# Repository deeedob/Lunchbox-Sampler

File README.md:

# Lunchbox Sampler

## Prerequisites

- [platformio](https://platformio.org/)
    - Teensyduino >= 1.58
    - gcc-arm-none-eabi >= 11.3.1

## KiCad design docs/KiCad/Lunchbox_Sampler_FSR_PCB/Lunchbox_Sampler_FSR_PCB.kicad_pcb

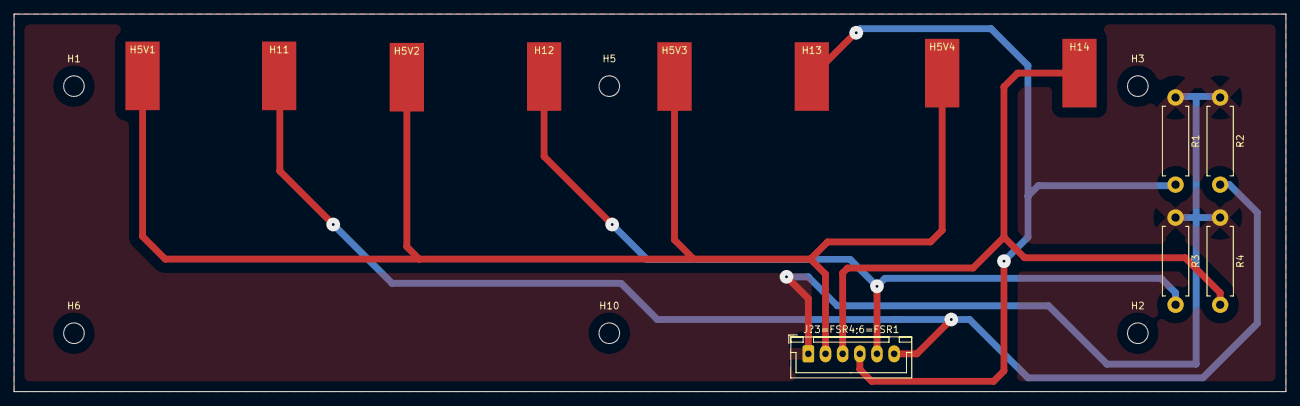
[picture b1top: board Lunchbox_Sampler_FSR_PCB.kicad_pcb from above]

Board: 2 copper layers, 185.3 x 55.0 mm, 19 parts (0 on the bottom side), 6 nets.

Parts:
H1, H2, H3, H5, H6, H10: MountingHole; MountingHole_3mm
H5V1, H5V2, H5V3, H5V4, H11, H12, H13, H14: MountingHole_Pad; SolderWirePad_1x01_SMD_5x10mm
J?3=FSR4;6=FSR1: 06JQ-BT; JST_XH_B6B-XH-A_1x06_P2.50mm_Vertical
R1, R2, R3, R4: R_Variable; R_Axial_DIN0411_L9.9mm_D3.6mm_P12.70mm_Horizontal

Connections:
GND: J?3=FSR4;6=FSR1.1, R1.1, R2.1, R3.1, R4.1
unnamed: H5V1.1, H5V2.1, H5V3.1, H5V4.1, J?3=FSR4;6=FSR1.2
unnamed: H11.1, J?3=FSR4;6=FSR1.6, R2.2
unnamed: H12.1, J?3=FSR4;6=FSR1.5, R3.2
unnamed: H13.1, J?3=FSR4;6=FSR1.4, R1.2
unnamed: H14.1, J?3=FSR4;6=FSR1.3, R4.2

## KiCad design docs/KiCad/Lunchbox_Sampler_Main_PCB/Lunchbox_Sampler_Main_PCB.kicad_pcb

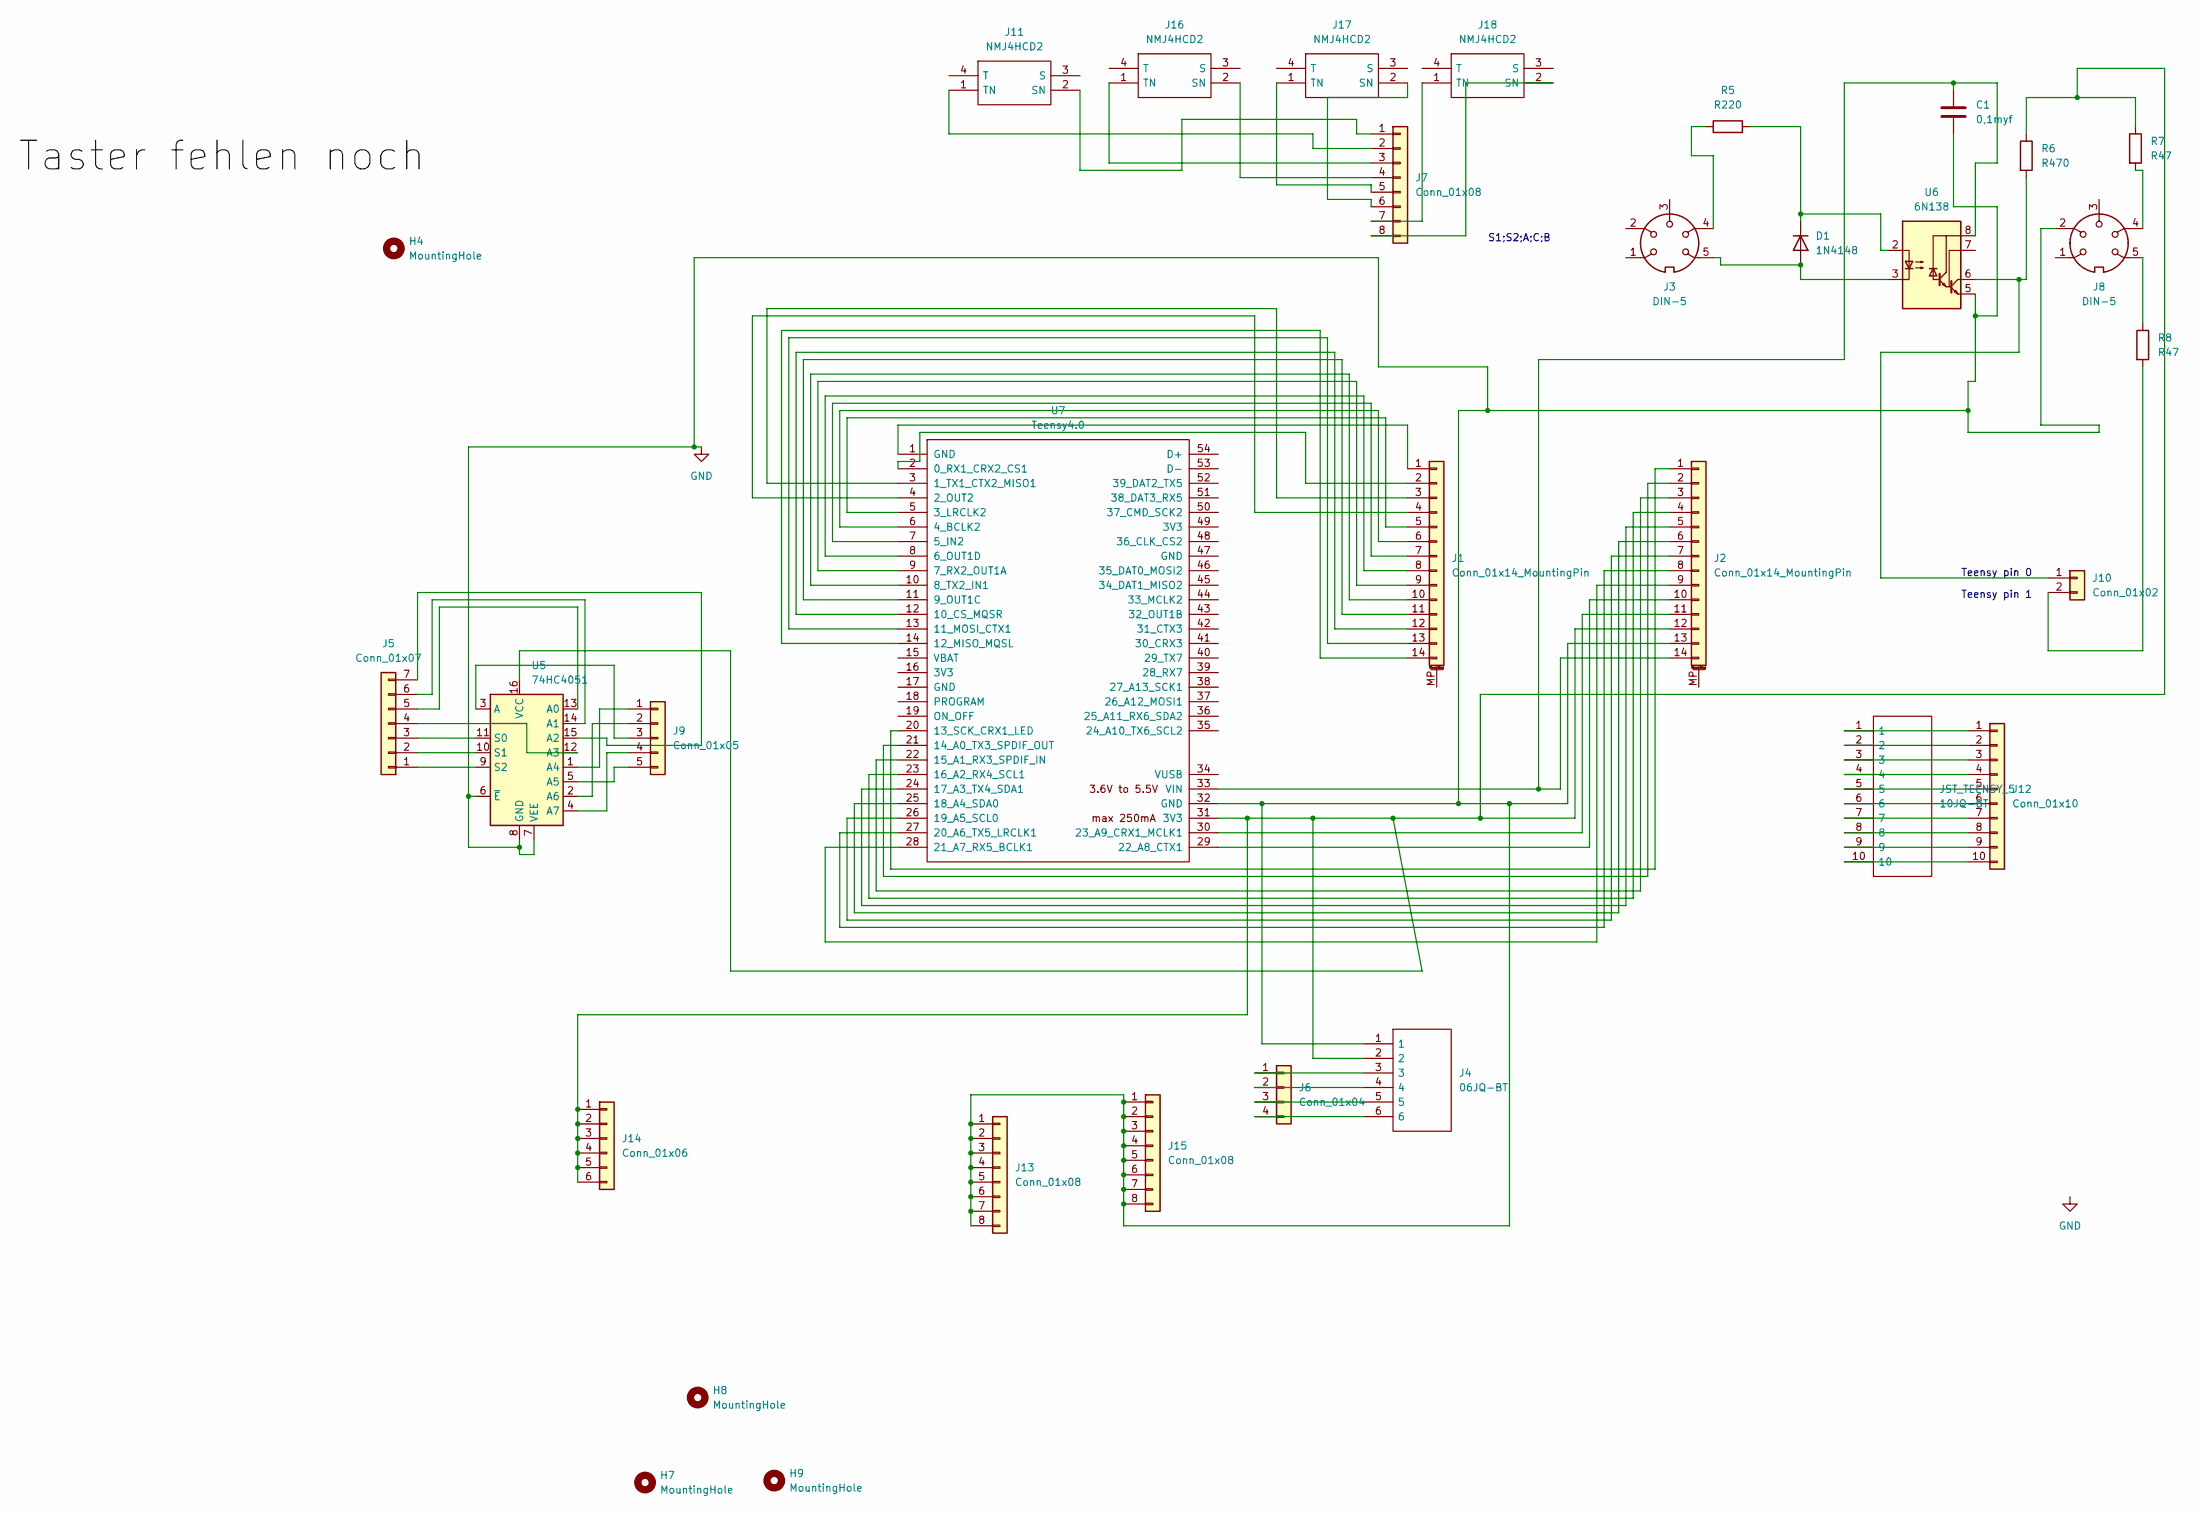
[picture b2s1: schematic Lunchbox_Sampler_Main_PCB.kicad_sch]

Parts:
C1: 0,1myf; CP_Radial_D8.0mm_P5.00mm
D1: 1N4148; D_DO-35_SOD27_P7.62mm_Horizontal
H4, H7, H8, H9: MountingHole; MountingHole_3mm
J1, J2: Conn_01x14_MountingPin; PinHeader_1x14_P2.54mm_Vertical
J3, J8: DIN-5; SDS-50J_MIDI_JACK
J4: 06JQ-BT; JST_XH_B6B-XH-A_1x06_P2.50mm_Vertical; Manufacturer_Part_Number 06JQ-BT
J5: Conn_01x07; PinHeader_1x07_P2.54mm_Vertical
J6: Conn_01x04; PinHeader_1x04_P2.54mm_Vertical
J7, J13, J15: Conn_01x08; PinHeader_1x08_P2.54mm_Vertical
J9: Conn_01x05; PinHeader_1x05_P2.54mm_Vertical
J10: Conn_01x02; PinHeader_1x02_P2.54mm_Vertical
J11, J16, J17, J18: NMJ4HCD2; Mouser Part Number 550-12202
J12: Conn_01x10; PinHeader_1x10_P2.54mm_Vertical
J14: Conn_01x06; PinHeader_1x06_P2.54mm_Vertical
JST_TEENSY_5: 10JQ-BT; JST_SH_SM10B-SRSS-TB_1x10-1MP_P1.00mm_Horizontal; Manufacturer_Part_Number 10JQ-BT; Mouser Part Number N/A
R5: R220; R_Axial_DIN0411_L9.9mm_D3.6mm_P12.70mm_Horizontal
R6: R470; R_Axial_DIN0411_L9.9mm_D3.6mm_P12.70mm_Horizontal
R7, R8: R47; R_Axial_DIN0411_L9.9mm_D3.6mm_P12.70mm_Horizontal
U5: 74HC4051; DIP794W53P254L1930H508Q16N
U6: 6N138; DIP762W56P254L966H508Q8N
U7: Teensy4.0; Teensy40

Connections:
GND: C1.2, J2.13, J4.1, J8.2, J13.1, J13.2, J13.3, J13.4, J13.5, J13.6, J13.7, J13.8, J15.1, J15.2, J15.3, J15.4, J15.5, J15.6, J15.7, J15.8, U5.6 (~E), U5.7 (VEE), U5.8 (GND), U6.5 (GND), U7.32 (GND)
unnamed: C1.1, J2.14, U6.8 (VCC), U7.33 (VIN)
unnamed: D1.1 (K), R5.2, U6.2 (C1)
unnamed: D1.2 (A), J3.5, U6.3 (C2)
unnamed: J1.1, U7.1 (GND)
unnamed: J1.2, U7.2 (0_RX1_CRX2_CS1)
unnamed: J1.3, U7.3 (1_TX1_CTX2_MISO1)
unnamed: J1.4, U7.4 (2_OUT2)
unnamed: J1.5, U7.5 (3_LRCLK2)
unnamed: J1.6, U7.6 (4_BCLK2)
unnamed: J1.7, U7.7 (5_IN2)
unnamed: J1.8, U7.8 (6_OUT1D)
unnamed: J1.9, U7.9 (7_RX2_OUT1A)
unnamed: J1.10, U7.10 (8_TX2_IN1)
unnamed: J1.11, U7.11 (9_OUT1C)
unnamed: J1.12, U7.12 (10_CS_MQSR)
unnamed: J1.13, U7.13 (11_MOSI_CTX1)
unnamed: J1.14, U7.14 (12_MISO_MQSL)
unnamed: J2.1, U7.20 (13_SCK_CRX1_LED)
unnamed: J2.2, U7.21 (14_A0_TX3_SPDIF_OUT)
unnamed: J2.3, U7.22 (15_A1_RX3_SPDIF_IN)
unnamed: J2.4, U7.23 (16_A2_RX4_SCL1)
unnamed: J2.5, U7.24 (17_A3_TX4_SDA1)
unnamed: J2.6, U7.25 (18_A4_SDA0)
unnamed: J2.7, U7.26 (19_A5_SCL0)
unnamed: J2.8, U7.27 (20_A6_TX5_LRCLK1)
unnamed: J2.9, U7.28 (21_A7_RX5_BCLK1)
unnamed: J2.10, U7.29 (22_A8_CTX1)
unnamed: J2.11, U7.30 (23_A9_CRX1_MCLK1)
unnamed: J3.4, R5.1
unnamed: J4.3, J6.1
unnamed: J4.4, J6.2
unnamed: J4.5, J6.3
unnamed: J4.6, J6.4
unnamed: J5.1, U5.9 (S2)
unnamed: J5.2, U5.10 (S1)
unnamed: J5.3, U5.11 (S0)
unnamed: J5.4, U5.12 (A3)
unnamed: J5.5, U5.13 (A0)
unnamed: J5.6, U5.14 (A1)
unnamed: J5.7, U5.15 (A2)
unnamed: J8.4, R7.2
unnamed: J8.5, R8.1
unnamed: J9.1, U5.1 (A4)
unnamed: J9.2, U5.2 (A6)
unnamed: J9.3, U5.3 (A)
unnamed: J9.4, U5.4 (A7)
unnamed: J9.5, U5.5 (A5)
unnamed: J10.1, R6.2, U6.6 (VO2)
unnamed: J10.2, R8.2
unnamed: J7.2, J11.1 (TN)
unnamed: J7.1, J11.2 (SN)
unnamed: J12.1, JST_TEENSY_5.1
unnamed: J12.2, JST_TEENSY_5.2
unnamed: J12.3, JST_TEENSY_5.3
unnamed: J12.4, JST_TEENSY_5.4
unnamed: J12.5, JST_TEENSY_5.5
unnamed: J12.6, JST_TEENSY_5.6
unnamed: J12.7, JST_TEENSY_5.7
unnamed: J12.8, JST_TEENSY_5.8
unnamed: J12.9, JST_TEENSY_5.9
unnamed: J12.10, JST_TEENSY_5.10
unnamed: J2.12, J4.2, J14.1, J14.2, J14.3, J14.4, J14.5, J14.6, R6.1, R7.1, U5.16 (VCC), U7.31 (3V3)
unnamed: J7.3, J16.1 (TN)
unnamed: J7.4, J16.2 (SN)
unnamed: J7.5, J17.1 (TN)
unnamed: J7.6, J17.2 (SN)
unnamed: J7.7, J18.1 (TN)
unnamed: J7.8, J18.2 (SN)

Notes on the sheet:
Teensy pin 1
Teensy pin 0
S1;S2;A;C;B

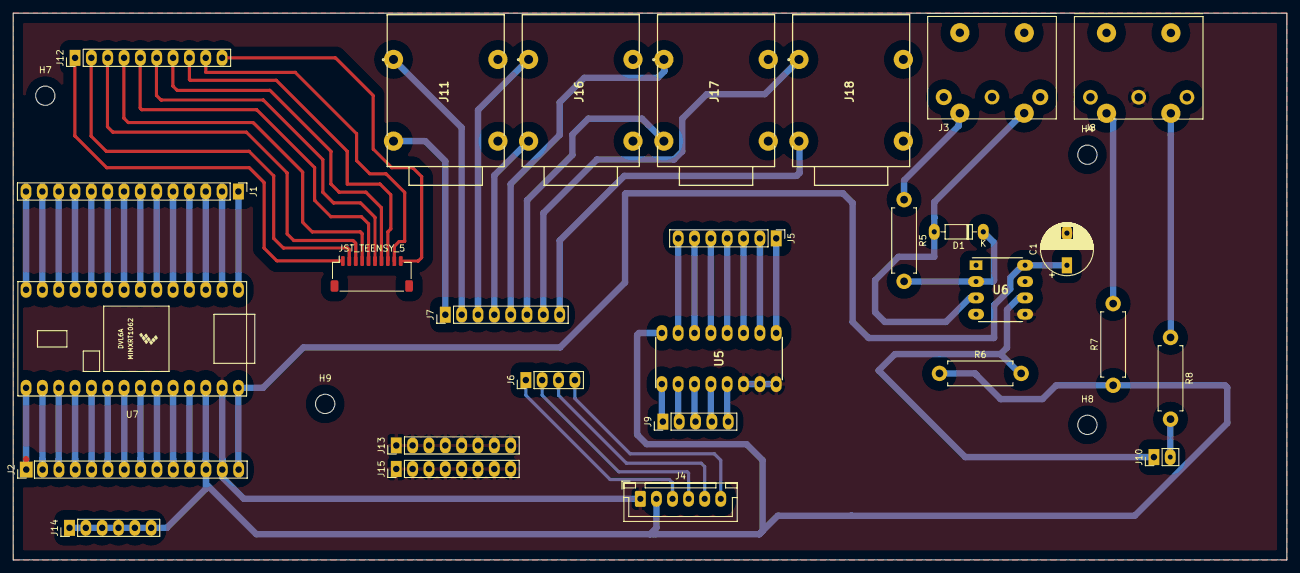
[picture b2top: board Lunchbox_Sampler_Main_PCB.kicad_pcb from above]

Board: 2 copper layers, 198.0 x 85.0 mm, 32 parts (0 on the bottom side), 68 nets.

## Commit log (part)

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2022-05-16 all test outcommented, execpt for loop
2022-05-16 wait until All Files are deleted
2022-05-17 minorChangesMemory
2022-05-20 Search Free Midi with Array, Print in .txt
2022-05-20 Update Settings as Array, Write in settings.txt;
2022-05-21 getSettings
2022-05-21 load settings update
2022-05-21 interrupt handler
2022-05-22 Comment and update Settings.txt when File is deleted
2022-06-09 Installing missing libraries and cleaning up headers
2022-06-09 Ignore CMakeLists.txt
2022-06-09 Revert platformio dependencies: Something is not quite right
2022-06-09 Move memory functions to own class
2022-06-12 defines
2022-06-12 Adjusting platformio.ini to needs (dependencies)
2022-06-12 Rewriting test.cpp to fit with newly created memory classes
2022-06-12 rtos
2022-06-12 Outsource of memory functions to own class (code still to be refactored)
2022-06-14 event-system structure
2022-06-14 interrupt handler impl
2022-06-15 started analog interrupts
2022-06-16 temporary commit outsourced Midi Class
2022-06-16 MemGeneric improve Singleton
2022-06-16 MemGeneric improve Singleton Part 2 (hpp)
2022-06-17 resolved circ dependencies -> dependency_graph.py!
2022-06-27 cleanup
2022-06-27 resources for testing
2022-06-27 Instruction for building the test
2022-06-27 fixed display bug
2022-06-27 print
2022-06-27 Update Hardware Test, test Flash
2022-06-27 multiplexer test
2022-06-28 Working stage: Memory Class (chaotic)
2022-06-28 docs
2022-06-28 remove latex docs
2022-06-28 pcb_case informations
2022-06-28 testing pins
2022-06-29 MemoryClass still chaotic no 2
2022-06-29 code review
2022-06-29 multiplexer working
2022-06-30 testing host midi
2022-06-30 pcb & case layout optimization
2022-06-30 started midi host testing
2022-06-30 todo - print and midi together
2022-07-02 fsr :: pin layout :: event rework
2022-07-02 fdps
2022-07-02 fsr and pots in seperate classes
2022-07-03 Interrupt System finished :: testing
2022-07-03 digital interrupt and audio working, no audio glitches!!
2022-07-04 using glue routines *_*, analog almost working
2022-07-05 Changing Singleton classes from pointer to reference
2022-07-05 analog and digital interrupts working
2022-07-05 fsr, pots, digital everything is working!! WTF
2022-07-07 pdfs
2022-07-21 event system almost completed
2022-07-22 preparing for big merge
2022-07-22 merged interrupts into main
2022-07-22 RecordMidi test
2022-07-22 prepareing for unidocs merge
2022-07-22 Huge chaos, much changes also in software design... status: testing of csv parsing done and working stable
2022-07-22 Refactoring of software design: introducing new classes MemSample unifying MemFlash and MemSD class (higher level abstraction class)
2022-07-22 preparing for main merge
2022-07-22 merged MIDI branch into main
2022-07-22 merged MemoryClass into main
2022-07-22 merged hw-test into main
2022-07-22 merged midi-host into main
2022-07-22 big changes :: refactores the whole repo structure :: please consult the README
2022-07-22 cleanup :: added clang-format :: LICENSE
2022-07-22 added main Application
2022-07-22 readme
2022-07-22 restored midi branch
2022-07-22 main dev branch
2022-07-23 added .idea for clion files
2022-07-23 readme, clion setup guide
2022-07-23 added srcFilter
2022-07-24 License : GPLv3 :: moved Doxyfile to docs :: rm .idea
2022-07-24 removed clang-format for now :: added clang-tidy
2022-07-24 clang-tidy
2022-07-24 Added Kicad Project
2022-07-24 added Kicad Files
2022-07-24 .gitignore
2022-07-24 KiCad Cleanup
2022-07-24 src_filter :: tidy -> fn now camelCase
2022-07-24 clang format and internal naming conventions in project setting
2022-07-24 Updated Kicad Project
2022-07-25 event system 99% finished
2022-07-25 hotfix
2022-07-25 restored memory branch
2022-07-25 structured and added interactive tests
2022-07-25 structured and added interactive tests, updated KiCad files
2022-07-26 event system now working with lbs singleton instance!
2022-07-26 Midi record update
2022-07-26 midi update
2022-07-26 created simple notes class
2022-07-26 fixed bug in pots
2022-07-26 update testing record Overdub
2022-07-26 Event System 100% working 100% integrated!
2022-08-03 multiple changes for Memory Class, forgotten to do subsequent commits
2022-08-08 update Notes Overdub
2022-08-08 Add library to play sound from Flash
2022-08-08 Add File interface for writing to MemFlash
2022-08-08 Add interface for reading File from SD to MemSD
2022-08-08 Finish loadSamplePack function and first drafts for playback
2022-08-08 Untrack original memory class files
2022-08-08 Removed SoundZ (does not compile) and friend function for playback added
2022-08-11 recordmidiinternnogrid
2022-08-12 changed code style :: pots now take const * const pointer
2022-08-12 rewrite of graphics system
2022-08-12 remove inner classes to write and read files, restructure with friend functions
2022-08-12 boolean --> bool
2022-08-12 started midi lib
2022-08-13 custom fonts :: graphics lib improvement
2022-08-13 window system impl
2022-08-14 rewrote graphics system :: added basic modules
2022-08-15 working on modules
2022-08-15 latest Kicad Project files
2022-08-16 update playSample (moved to MemFlash) and fix different problems in function declarations (some classes did not associate function with their implementation)
2022-08-16 load SamplePack01 for testing
2022-08-16 restructured modules
2022-08-16 improved PCB for soldering parts
2022-08-17 modules working almost 100%
2022-08-17 removed old lbs-ui
2022-08-17 modules need implementation
2022-08-17 updated fontconverter
2022-08-17 updated from dev
2022-08-17 added samplepack
2022-08-18 initialized new module
2022-08-18 structured memory module
2022-08-18 New Memory classes under lbs-memory, big restructure
2022-08-18 remove unused code
2022-08-18 remove Singleton
2022-08-18 line break
2022-08-18 Switch to new memory class
2022-08-18 test load File to flash and getFileList
2022-08-18 started audio impl
2022-08-18 Flash Pin and FlashSize, Settings file and Samplepack dir define constants in define_t40.hpp
2022-08-18 Copy constructor fix in Window class (Adafruit bug on lucas' machine)
2022-08-18 Basename function to mem_flash
2022-08-19 fixed weird Adafruit GFX bug
2022-08-19 Midi Visualisation static
2022-08-19 Midi Visualisation still static,but display of send in note
2022-08-20 add eraseFlash function
2022-08-20 fix Window bug in Copy Constructor: adjust prototype in class definition (remove width and height from copy constructor prototype)
2022-08-20 2ns try, error on merging from origin/memorymain: fix Window bug in Copy Constructor: adjust prototype in class definition (remove width and height from copy constructor prototype)
2022-08-20 basic dynamic audio setup
2022-08-20 basic midi setup
2022-08-20 feature getSampleNames from given Samplepack and loadSamplepack onto Flash
2022-08-20 add proper samplepack to res folder
2022-08-20 write test for upload function (Samples to Flash)
2022-08-20 close files in transferToFlash after use
2022-08-20 main function lost during rebase or merge: rewriting test for upload function (Samples to Flash)
2022-08-20 test loading Samplepack03 (Samplepack01 with less samples) onto flash and Playing with playRawaudio function
2022-08-20 cosmetics in debug output of transfertoflash (space before filename)
2022-08-20 added midi naming file :: midi listener
2022-08-20 comment on AudioMemory call
2022-08-20 cleanup :: readme samplepacks init
2022-08-20 added ffmpeg batch converter script
2022-08-20 main memory from std::string -> String, todos
2022-08-20 feature: skip wave header on wave files
2022-08-20 feature: skip wave header on wave files, make filenames on flash short (only numbers)
2022-08-20 rename transferSingleToFlash to transferSampleToFlash
2022-08-20 converted samplepack to mono :: update ffmpeg batch script :: added wav2trw.c from https://github.com/FrankBoesing/Teensy-PlayRawFromSerialFlash to experiment!
2022-08-21 added 4, 8, 16 polyphony to audio -- sadly not smooth enough
2022-08-24 STARTING WITH UI, LOAD SAMPLES
2022-08-25 LOAD SAMPLES with CHOOSEMIDI
2022-08-25 LOAD SAMPLES BUGFIX
2022-08-26 UPDATE MODULE_LOAD
2022-08-26 UPDATE MODULE_LOAD ADD SAMPLEPACKS
2022-08-26 UPDATE MODULE_LOAD Bugg Fix
2022-09-06 MODULE SOUND MANAGER SETUP
2022-09-07 MODULE AUDIO SETUP WINDOW UPDATE DRAWROTARY && DRAWCIRCLE(unfitting Name, change later)
2022-09-07 sample polyphony working
2022-09-07 pcb updated
2022-09-07 updated gitignore
2022-09-07 added audio standalone test
2022-09-07 UPDATE MODULE LOAD AND SOUND MANAGER, AUDIO, STILL MESSY WITH OLD CLASSES; NEEDS CLEAN UP
2022-09-08 UPDATE DETAIL EFFECTS
2022-09-08 fsr pads almost working
2022-09-10 start implementing ui modules
2022-09-11 polished module_load now with a progress bar
2022-09-11 started working on the audio module
2022-09-12 CSV parsing working again (without CSV Parser) and Samplepacks too large for flash are shortened
2022-09-12 add midi lib
2022-09-12 minor fixes
2022-09-12 getSampleFromNote function (returning mapped Sample) and some debug msg cleaning
2022-09-12 flashempty and free space related functions
2022-09-12 getAllSamplePacks
2022-09-13 MappingFile functions and tidying
2022-09-13 final refactor and testing
2022-09-13 comments
2022-09-13 comments updated
2022-09-13 prepare class as todo list for integrating every missing function one by one
2022-09-13 rename initMemory to init
2022-09-13 integrate getFreeSpaceFromSD
2022-09-13 update comment on getFilelistFromFlash()
2022-09-13 integrate getFreeSpaceFromFlash() and flashEmpty()
2022-09-13 integrate getNoteName(midiNote) fix broken comment at getFreeSpaceFromFlash() and make noInterrupt/interrupt() calls in flashEmpty()
2022-09-13 update getSampleNamesFromPack to exclude everything that is not raw or wave file (needs integration of AUDIOTYPE and getAudioType())
2022-09-13 update loadSamplepack (stripSize by if total sum of bytes too large) [requires createStdMappingFile(), getRawAudioSize() and findPayload()] and update transferSingleToFlash in order to support partia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
2022-09-14 update loadSamplepack (stripSize by if total sum of bytes too large) [requires createStdMappingFile(), loadMappingFile(), getRawAudioSize() and findPayload()] and update transferSingleToFlash in orde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
    loadMappingFile() needs the mapping arrays parsePlaybackMode and pretty much all member variables still missing (pitches, sampleMapping, modeMapping)
2022-09-14 integrate getLoadedPackName()
2022-09-14 integrate getSampleFromNote()
2022-09-14 integrate setSampleForNote)
2022-09-14 integrate deleteMappingFile()
2022-09-14 integrate createAllStdMappingFiles()
2022-09-14 add interrupts / nointerrupts calls to parsePlaybackMode and integrate saveCurrentMappingToFile() (needs parseStringFromPlaybackMode())
2022-09-14 integrate printMapping()
2022-09-14 adding missing comments and updating getSampleNamesFromPack (sorting filelist for right order of mapping)
2022-09-14 rename getSampleFromNote to getSample (to be called on midi event)
2023-05-13 Prepare for refactoring
2023-05-13 Purged repo and updated to gcc-arm-none-eabi 11.3.1
    Teensy has updated to gcc-arm-none-eabi 11.3.1 which enables the use of
    modern c++ features, purged the repo. Additionally, the the repo is now
    MIT licensed.
2023-05-14 Introduce: Logger and add initial logging tests
2023-05-14 Add structure for the graphics engine and create pin-layout
